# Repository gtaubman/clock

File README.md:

# Digital LED Clock

This project contains KiCad board schematics, PCB layouts, and firmware for my
digital clock.

The clock features buttons to set the time, a hold button to aid in syncing the
clock to another time source, and a switch to toggle the right-most display
between showing seconds and the current temperature as reported by the real-time
clock.

The clock is divided into two PCBs:

## The LED Board

Schematic:

![LED Board
Schematic](https://raw.githubusercontent.com/gtaubman/clock/master/images/led_schematic.png)

PCB Layout:

![LED Board
PCB](https://raw.githubusercontent.com/gtaubman/clock/master/images/led_pcb.png)

PCB fabricated by OSH Park:

This board contains:

1.  Three 2-digit 7-segment displays (Lite-On LTG-5612AG).
1.  A TLC5916 constant-current LED driver to drive the LEDs.
1.  A 0.1 uF decoupling capacitor for the TLC5916.
1.  A 1000 Ohm resistor to set the current allowed through the TLC5916.
1.  6 power pins to drive the individual digits.
1.  3 serial data pins to drive the TLC5916 (serial data, serial clock, latch).
1.  2 pins for power and ground for the TLC5916.

## The Clock Board

Schematic:

PCB Layout:

PCB fabricated by OSH Park:

The clock board is responsible for driving the entire clock logic, as well as
interfacing with the real-time clock chip, and allowing user control over the
clock functionality.  It consists of:

1.  One Atmega 328pu running the show.
1.  One DS3231 real-time clock, communicating with the AVR over i2c.
1.  One 74HC595 shift register to control which digit is powered on.
1.  6 transistors to power on digits.
1.  6 1k, 2 4.7k, and 2 10k resistors.
1.  4 push buttons for setting the time and temperature display modes.
1.  3 decoupling capacitors.
1.  2 10uF capacitors and a 7805 voltage regulator for supplying power.
1.  Pins to send power, data, and chip power to the LED board.
1.  An optional LED to indicate when the board is powered on.

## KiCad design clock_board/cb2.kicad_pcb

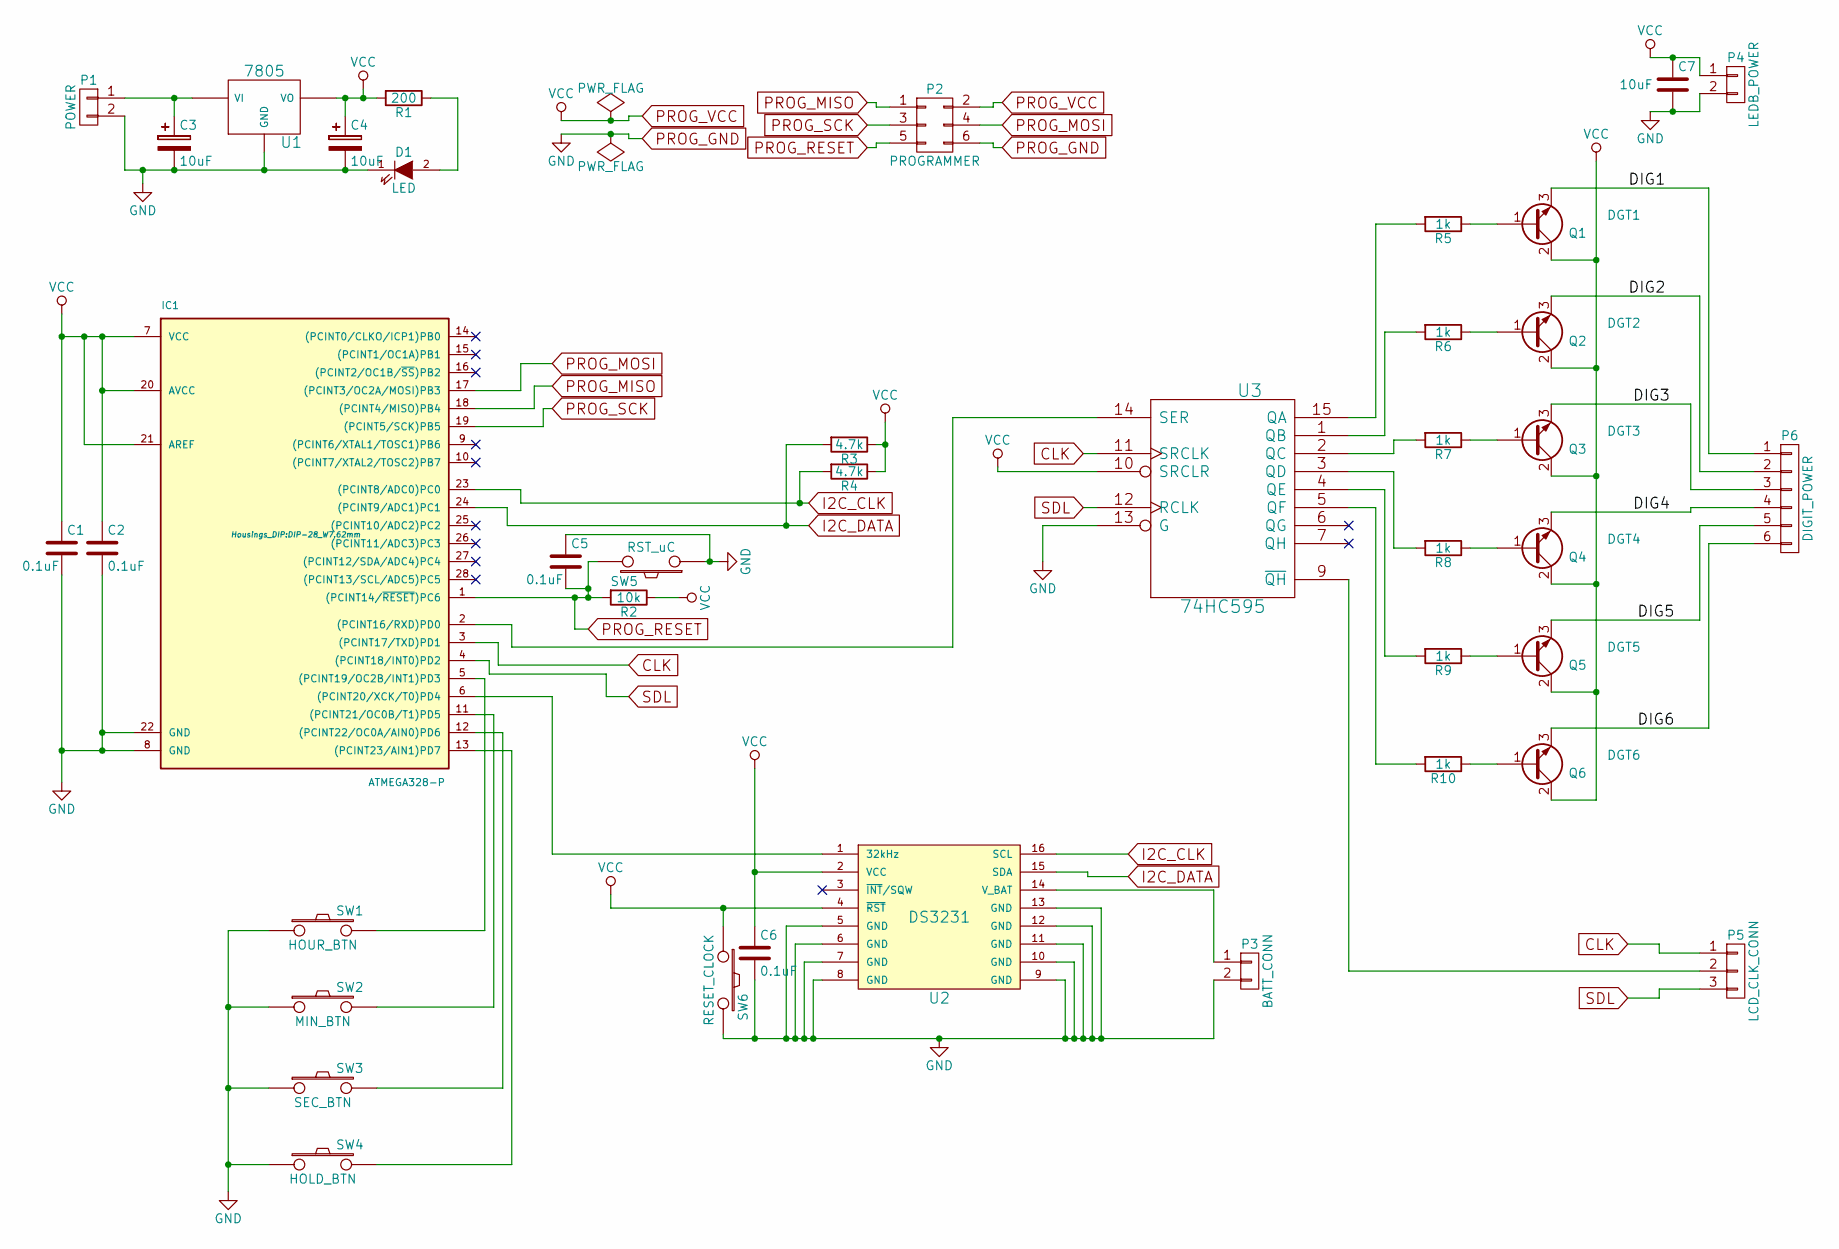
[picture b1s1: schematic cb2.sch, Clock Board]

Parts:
C1, C2, C5, C6: 0.1uF; C_Disc_D3_P2.5
C3, C4: 10uF; Elko_vert_11.2x6.3mm_RM2.5
C7: 10uF; Elko_vert_20x10mm_RM2.5
D1: LED; LED-3MM
IC1: ATMEGA328-P; DIP-28_W7.62mm
P1: POWER; Pin_Header_Straight_1x02
P2: PROGRAMMER; Pin_Header_Straight_2x03
P3: BATT_CONN; PINHEAD1-2
P4: LEDB_POWER; Pin_Header_Straight_1x02
P5: LCD_CLK_CONN; Pin_Header_Straight_1x03
P6: DIGIT_POWER; Pin_Header_Straight_1x06
Q1: DGT1; TO-92_Inline_Narrow_Oval
Q2: DGT2; TO-92_Inline_Narrow_Oval
Q3: DGT3; TO-92_Inline_Narrow_Oval
Q4: DGT4; TO-92_Inline_Narrow_Oval
Q5: DGT5; TO-92_Inline_Narrow_Oval
Q6: DGT6; TO-92_Inline_Narrow_Oval
R1: 200; Resistor_Horizontal_RM10mm
R2: 10k; Resistor_Horizontal_RM10mm
R3, R4: 4.7k; Resistor_Horizontal_RM10mm
R5, R6, R7, R8, R9, R10: 1k; Resistor_Horizontal_RM10mm
SW1: HOUR_BTN; SW_PUSH_SMALL
SW2: MIN_BTN; SW_PUSH_SMALL
SW3: SEC_BTN; SW_PUSH_SMALL
SW4: HOLD_BTN; SW_PUSH_SMALL
SW5: RST_uC; SW_PUSH_SMALL
SW6: RESET_CLOCK; SW_PUSH_SMALL
U1: 7805; TO-220
U2: DS3231; SO-16-N
U3: 74HC595; DIP-16_W7.62mm

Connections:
/DIG1: P6.1, Q1.3 (E)
/DIG2: P6.2, Q2.3 (E)
/DIG3: P6.3, Q3.3 (E)
/DIG4: P6.4, Q4.3 (E)
/DIG5: P6.5, Q5.3 (E)
/DIG6: P6.6, Q6.3 (E)
CLK: IC1.3 ((PCINT17/TXD)PD1), P5.1, U3.11 (SRCLK)
I2C_CLK: IC1.23 ((PCINT8/ADC0)PC0), R4.2, U2.16 (SCL)
I2C_DATA: IC1.24 ((PCINT9/ADC1)PC1), R3.2, U2.15 (SDA)
unnamed: C3.1, P1.1, U1.1 (VI)
unnamed: D1.2 (A), R1.1
unnamed: IC1.2 ((PCINT16/RXD)PD0), U3.14 (SER)
unnamed: IC1.5 ((PCINT19/OC2B/INT1)PD3), SW1.2
unnamed: IC1.6 ((PCINT20/XCK/T0)PD4), U2.1 (32kHz)
unnamed: IC1.11 ((PCINT21/OC0B/T1)PD5), SW2.2
unnamed: IC1.12 ((PCINT22/OC0A/AIN0)PD6), SW3.2
unnamed: IC1.13 ((PCINT23/AIN1)PD7), SW4.2
unnamed: P3.1, U2.14 (V_BAT)
unnamed: P5.2, U3.9 (~QH)
unnamed: Q1.1 (B), R5.1
unnamed: Q2.1 (B), R6.1
unnamed: Q3.1 (B), R7.1
unnamed: Q4.1 (B), R8.1
unnamed: Q5.1 (B), R9.1
unnamed: Q6.1 (B), R10.1
unnamed: R5.2, U3.15 (QA)
unnamed: R6.2, U3.1 (QB)
unnamed: R7.2, U3.2 (QC)
unnamed: R8.2, U3.3 (QD)
unnamed: R9.2, U3.4 (QE)
unnamed: R10.2, U3.5 (QF)
PROG_GND: C1.2, C2.2, C3.2, C4.2, C5.1, C6.2, C7.2, D1.1 (K), IC1.8 (GND), IC1.22 (GND), P1.2, P2.6, P3.2, P4.2, SW1.1, SW2.1, SW3.1, SW4.1, SW5.1, SW6.2, U1.2 (GND), U2.5 (GND), U2.6 (GND), U2.7 (GND), U2.8 (GND), U2.9 (GND), U2.10 (GND), U2.11 (GND), U2.12 (GND), U2.13 (GND), U3.8 (GND), U3.13 (G)
PROG_MISO: IC1.18 ((PCINT4/MISO)PB4), P2.1
PROG_MOSI: IC1.17 ((PCINT3/OC2A/MOSI)PB3), P2.4
PROG_RESET: C5.2, IC1.1 ((PCINT14/~RESET~)PC6), P2.5, R2.2, SW5.2
PROG_SCK: IC1.19 ((PCINT5/SCK)PB5), P2.3
PROG_VCC: C1.1, C2.1, C4.1, C6.1, C7.1, IC1.7 (VCC), IC1.20 (AVCC), IC1.21 (AREF), P2.2, P4.1, Q1.2 (C), Q2.2 (C), Q3.2 (C), Q4.2 (C), Q5.2 (C), Q6.2 (C), R1.2, R2.1, R3.1, R4.1, SW6.1, U1.3 (VO), U2.2 (VCC), U2.4 (~RST), U3.10 (SRCLR), U3.16 (VCC)
SDL: IC1.4 ((PCINT18/INT0)PD2), P5.3, U3.12 (RCLK)

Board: 2 copper layers, 41 parts (0 on the bottom side), 38 nets, no tracks yet.

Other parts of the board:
REF1, REF2: 1pin

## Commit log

2015-09-03 Add an initial README.
2015-09-03 Initial firmware commit.
    Add firmware for the clock, which can currently set the time, display the time,
    and optionally replace the seconds display with a fahrenheit temperature
    display.
2015-09-03 Initial commit of KiCad files for clock LED board.
2015-09-03 Initial commit of KiCad files for clock board.
2015-09-06 Make the port for serial data be a #define.
2015-09-06 Update a TODO for moving to proper clock board.
2015-09-06 Remove an unused delay_ms() function.
2015-09-12 Add a pixel clock header image.
2015-09-12 Add the pixel clock image to the README.
2015-09-13 A little more documentation of the two boards' BOMs.
2015-09-13 Add an image of the bare LED board.
2015-09-13 Reword the description of the toggling seconds / temp.
2015-09-18 Add images of the led board schematic and PCB.
2015-09-18 Add to the README images of LED PCB and Schematic.
2015-09-28 At midnight, show both hour zeros instead of just one zero.
2015-10-10 Removed clock reset button. Improved PCB layout.
2015-10-10 Updated footprints for DS3231, 4.7k resistors, and battery connection.
2015-11-01 Read the time one 1-second intervals as dictated by the DS3231 square wave.
    Fixed a bug in RTC I2C communications where all read bytes were being BCD
    decoded.
    Got rid of the unused LED pin.
    Enabled the 1Hz square wave on the DS3231.
    Changed the schematic to no longer use the 32KHz wave and instead connect the
    1Hz square wave to INT1, and only trigger INT1 on falling edges.
2015-11-01 Add the pullup resistor for the DS3231 square wave.
2015-11-01 Tidy up enabling square waves.
2015-11-01 Keep the last digit from pulsing on the second.
    Now that fetching the time is driven by interrupt, the time taken to fetch the
    time would leave the last digit in the cycle enabled for a fractionally longer
    amount of time. This causes the last digit to slightly visibly pulse brighter
    when fetching the time.
    Disabling the last digit right before fetching the time fixes the problem.
2015-11-01 Add a comment describing why we disable the last digit when fetching the time.
2015-11-08 Allow setting the hours, minutes, and seconds.
    Introduce a button struct which performs button debouncing.
    Introduce rtc functions to allow incrementing hours, mins, and seconds.
2015-11-08 Change the seconds button to be a seconds hold toggle.
    Also cleanup the button pressed logic.
2015-11-08 Add is_button_lifted() to check for button up.
    Also document the button class.
2015-11-08 Forgot to change refactored button function names in c file.
2015-11-10 Clock board Rev A with routing and placement.
2015-11-22 Add images for the clock board PCB and schematic to the README.
2015-11-27 Switch the i2c pins to the final board layout.
2015-11-27 Implement the temperature toggle button.
2015-11-27 Add an image of the bare clock board.
2015-11-27 Update README to include bare clock board PCB.
2015-11-27 Add images of LED and Clock boards populated.
2015-11-27 Fix README images (png -> jpg).
2015-12-05 Add image of clock in case.
2015-12-05 Finish clock board BOM.
2015-12-23 Allow setting the RTC to be in 12-hour mode.
2015-12-23 Add a .gitignore file for .o, .swp, .hex, and .elf files.
2016-04-02 Add an image of the inside of the clock connected.
2016-04-02 Update README with new imagery.
